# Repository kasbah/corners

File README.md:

# Corners

An experiment in making triangle shaped LED pieces for solder sculpting.

[Kitspace page](https://kitspace.org/boards/github.com/kasbah/corners)

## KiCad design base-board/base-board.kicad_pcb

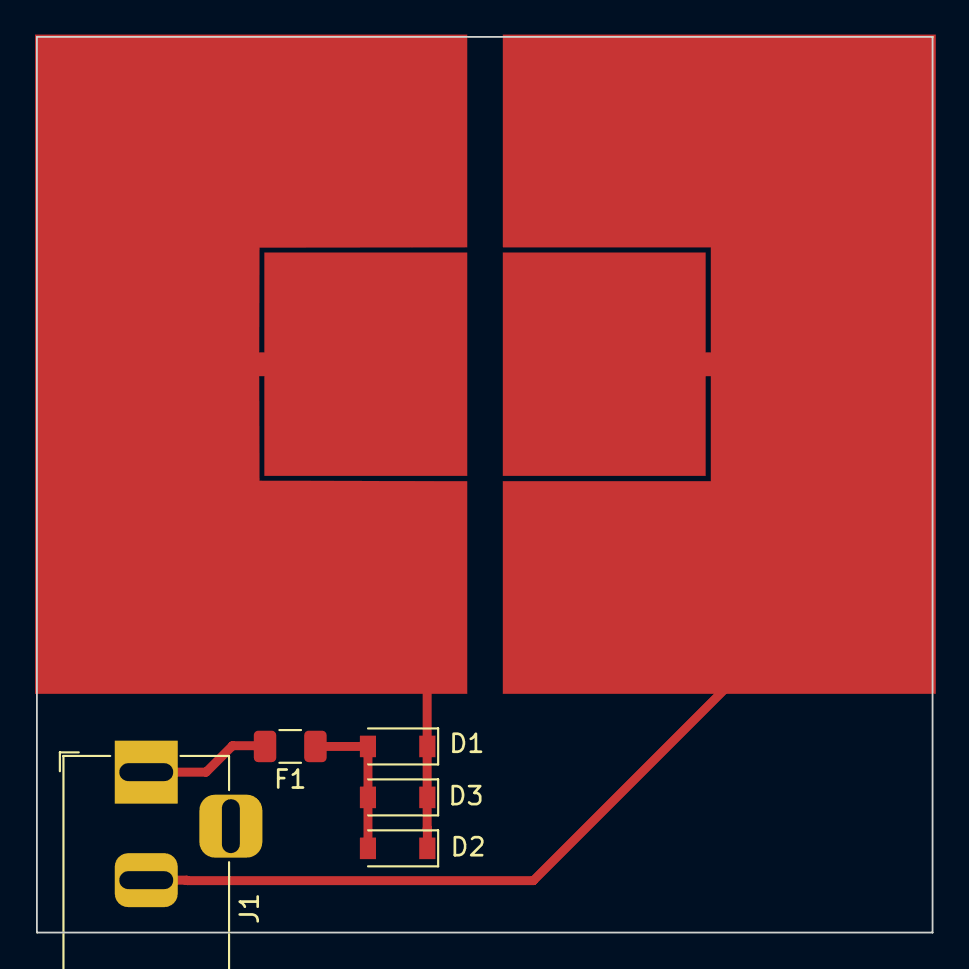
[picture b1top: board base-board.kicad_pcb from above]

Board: 2 copper layers, 49.8 x 49.8 mm, 6 parts (0 on the bottom side), 3 nets.

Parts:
D1, D2, D3: D; D_SOD-123
F1: Polyfuse; Fuse_1206_3216Metric
J1: Barrel_Jack_MountingPin; BarrelJack_Horizontal
J2: Conn_01x01_Female; base_outline

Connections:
+: D1.1, D2.1, D3.1
unnamed: D1.2, D2.2, D3.2, F1.1
unnamed: F1.2, J1.1

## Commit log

2018-10-05 Start panellizing corners
2018-10-06 Add base-board
2018-10-06 Plot and make ready for kitspace
2018-10-06 Add readme
2018-10-06 Add part selection to BOM
2018-10-06 Fix gerbers path
2018-10-06 Add DC barrel jack to BOM
2018-10-06 Switch to surface mount barrel jack
